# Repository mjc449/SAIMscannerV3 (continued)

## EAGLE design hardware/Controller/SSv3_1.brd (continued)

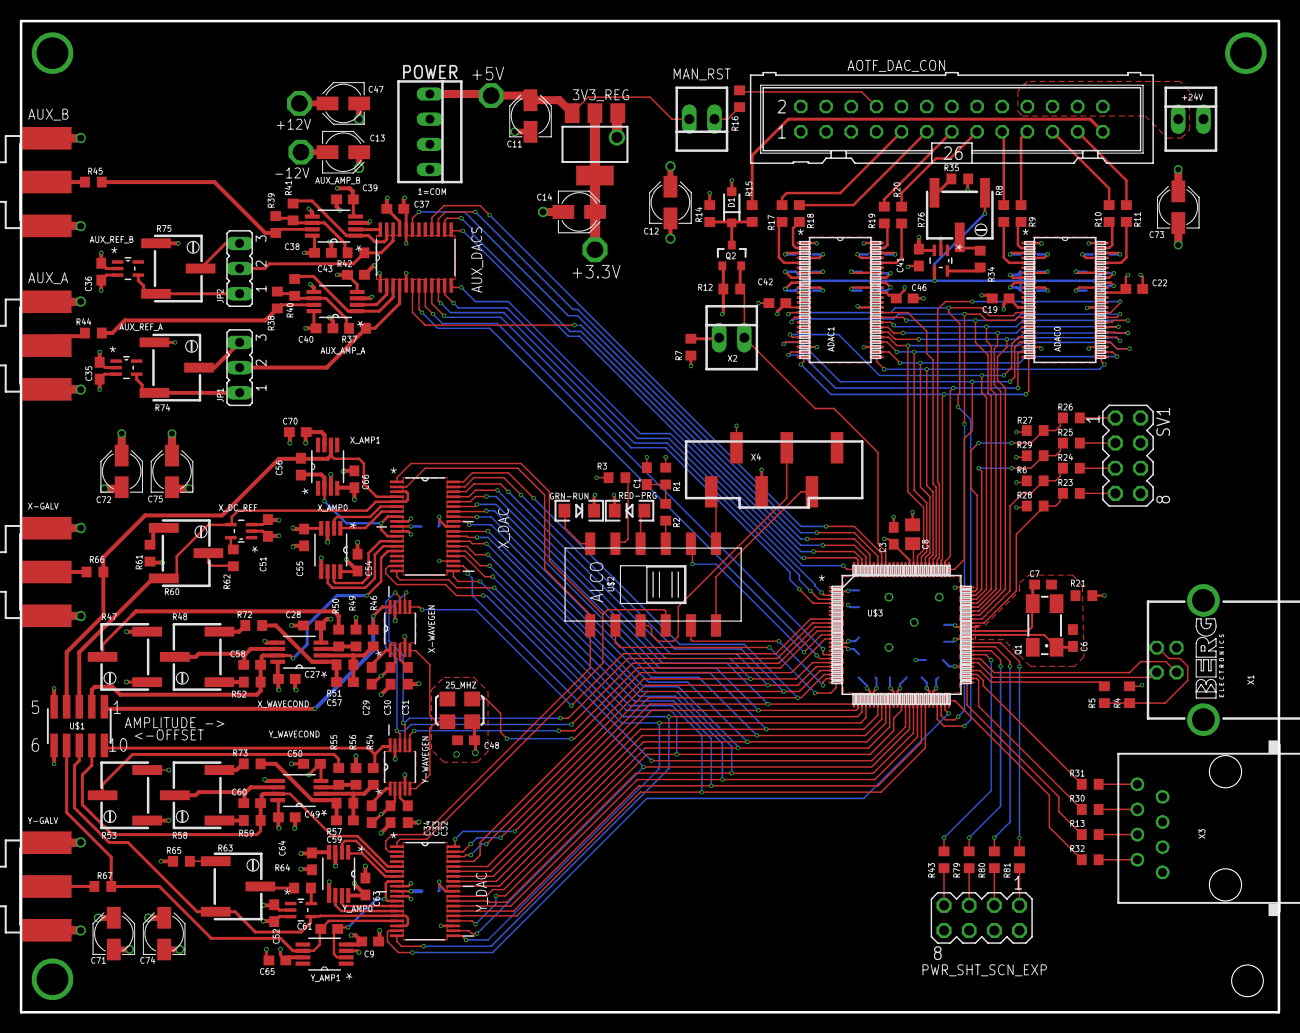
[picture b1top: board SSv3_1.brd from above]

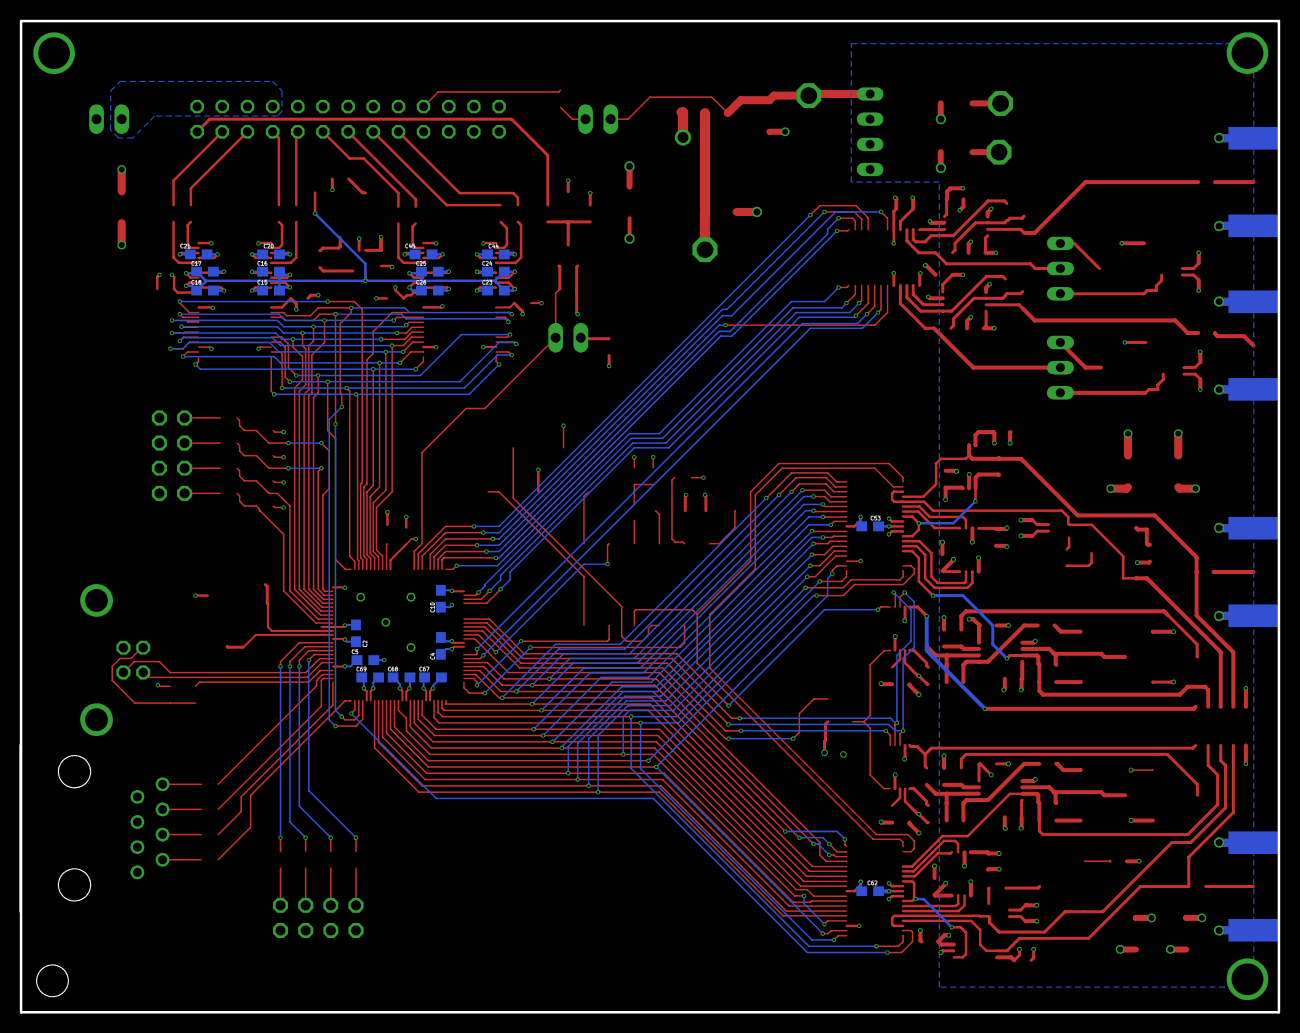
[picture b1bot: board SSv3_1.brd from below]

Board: 4 copper layers, 127.0 x 100.1 mm, 197 parts (21 on the bottom side), 190 nets.

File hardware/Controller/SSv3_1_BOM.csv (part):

"Part";"Value";"Device";"Package";"Description";"MANUFACTURER_PART_NUMBER";"MF";"MPN";"OC_FARNELL";"OC_NEWARK";"PACKAGE";"PROD_ID";"SUPPLIER";"VALUE";"VENDOR";
"+3.3V";"TESTPOINT";"TESTPOINT";"TESTPOINT";"";"";"";"";"";"";"";"";"";"";"";
"+5V";"TESTPOINT";"TESTPOINT";"TESTPOINT";"";"";"";"";"";"";"";"";"";"";"";
"+12V";"TESTPOINT";"TESTPOINT";"TESTPOINT";"";"";"";"";"";"";"";"";"";"";"";
"+24V";"AOTF_SUPPLY";"2PINHEADER";"22-23-2021";"2 pin 0.100" Header for 2 pin header pigtails I get from Allelectronics.";"";"";"";"";"";"";"";"";"";"";
"-12V";"TESTPOINT";"TESTPOINT";"TESTPOINT";"";"";"";"";"";"";"";"";"";"";"";
"3V3_REG";"AP1117";"AP1117E33G_REG";"SOT223";"3.3 volt 1 amp regulator SOT223 case";"";"";"";"";"";"";"";"";"";"";
"25_MHZ";"ASFL1";"ASFL1";"ASF";"CRYSTAL CLOCK OSCILLATORS";"";"Abracon Corporation";"ASFL1-125.000MHZ-EC-T";"1838931";"19M1882";"";"";"";"";"";
"ADAC0";"AD5583YRVZ";"AD5583YRVZ";"RV_48";"";"AD5583YRVZ";"";"";"";"";"";"";"";"";"Vendor";
"ADAC1";"AD5583YRVZ";"AD5583YRVZ";"RV_48";"";"AD5583YRVZ";"";"";"";"";"";"";"";"";"Vendor";
"ADAC_REF";"ADR01";"ADR03AKSZ-REEL7";"SOT65P210X110-5N";"Ultracompact, Precision 10.0 V/5.0 V/2.5 V/3.0 V Voltage References";"";"";"ADR03AKSZ-REEL7";"1838919";"59K2675";"SC70-5";"";"Analog Devices";"";"";
"AOTF_DAC_CON";"TO_PNLMNT_DB25";"ML26";"ML26";"HARTING";"";"";"";"unknown";"unknown";"";"";"";"";"";
"AUX_A";"";"SMA_SMT";"SIDE_MOUNTSMA";"SMA 50 Ohm End Launch Jack Receptacle - Round Contact";"";"";"";"";"";"";"";"";"";"";
"AUX_AMP_A";"OP2177";"OP2177ARMZ-R7";"SOP65P490X110-8N";"Operational Amplifiers";"";"";"OP2177ARMZ-R7";"-";"71P5435";"MSOP-8";"";"Analog Devices";"";"";
"AUX_AMP_B";"OP2177";"OP2177ARMZ-R7";"SOP65P490X110-8N";"Operational Amplifiers";"";"";"OP2177ARMZ-R7";"-";"71P5435";"MSOP-8";"";"Analog Devices";"";"";
"AUX_B";"";"SMA_SMT";"SIDE_MOUNTSMA";"SMA 50 Ohm End Launch Jack Receptacle - Round Contact";"";"";"";"";"";"";"";"";"";"";
"AUX_DACS";"AD5440YRUZ";"AD5440YRUZTSSOP-24";"SOP65P640X120-24N";"";"";"";"";"";"";"";"";"";"";"";
"AUX_REF_A";"ADR01";"ADR03AKSZ-REEL7";"SOT65P210X110-5N";"Ultracompact, Precision 10.0 V/5.0 V/2.5 V/3.0 V Voltage References";"";"";"ADR03AKSZ-REEL7";"1838919";"59K2675";"SC70-5";"";"Analog Devices";"";"";
"AUX_REF_B";"ADR01";"ADR03AKSZ-REEL7";"SOT65P210X110-5N";"Ultracompact, Precision 10.0 V/5.0 V/2.5 V/3.0 V Voltage References";"";"";"ADR03AKSZ-REEL7";"1838919";"59K2675";"SC70-5";"";"Analog Devices";"";"";
"C1";"0.1uF";"C-USC0603";"C0603";"CAPACITOR, American symbol";"";"";"";"";"";"";"";"";"";"";
"C2";"0.1uF";"C-USC0603";"C0603";"CAPACITOR, American symbol";"";"";"";"";"";"";"";"";"";"";
"C3";"0.1uF";"C-USC0603";"C0603";"CAPACITOR, American symbol";"";"";"";"";"";"";"";"";"";"";
"C4";"0.1uF";"C-USC0603";"C0603";"CAPACITOR, American symbol";"";"";"";"";"";"";"";"";"";"";
"C5";"0.1uF";"C-USC0603";"C0603";"CAPACITOR, American symbol";"";"";"";"";"";"";"";"";"";"";
"C6";"30pF";"C-USC0603";"C0603";"CAPACITOR, American symbol";"";"";"";"";"";"";"";"";"";"";
"C7";"30pF";"C-USC0603";"C0603";"CAPACITOR, American symbol";"";"";"";"";"";"";"";"";"";"";
"C8";"10uF";"C-USC0805";"C0805";"CAPACITOR, American symbol";"";"";"";"";"";"";"";"";"";"";
"C9";"0.1uF";"C-USC0603";"C0603";"CAPACITOR, American symbol";"";"";"";"";"";"";"";"";"";"";
"C10";"0.1uF";"C-USC0603";"C0603";"CAPACITOR, American symbol";"";"";"";"";"";"";"";"";"";"";
"C11";"10uF";"CPOL-USB";"PANASONIC_B";"POLARIZED CAPACITOR, American symbol";"";"";"";"";"";"";"";"";"";"";
"C12";"10uF";"CPOL-USB";"PANASONIC_B";"POLARIZED CAPACITOR, American symbol";"";"";"";"";"";"";"";"";"";"";
"C13";"10uF";"CPOL-USB";"PANASONIC_B";"POLARIZED CAPACITOR, American symbol";"";"";"";"";"";"";"";"";"";"";
"C14";"10uF";"CPOL-USB";"PANASONIC_B";"POLARIZED CAPACITOR, American symbol";"";"";"";"";"";"";"";"";"";"";
"C15";"0.1uF";"C-USC0603";"C0603";"CAPACITOR, American symbol";"";"";"";"";"";"";"";"";"";"";
"C16";"0.1uF";"C-USC0603";"C0603";"CAPACITOR, American symbol";"";"";"";"";"";"";"";"";"";"";
"C17";"0.1uF";"C-USC0603";"C0603";"CAPACITOR, American symbol";"";"";"";"";"";"";"";"";"";"";
"C18";"0.1uF";"C-USC0603";"C0603";"CAPACITOR, American symbol";"";"";"";"";"";"";"";"";"";"";
"C19";"0.1uF";"C-USC0603";"C0603";"CAPACITOR, American symbol";"";"";"";"";"";"";"";"";"";"";
"C20";"0.1uF";"C-USC0603";"C0603";"CAPACITOR, American symbol";"";"";"";"";"";"";"";"";"";"";
"C21";"0.1uF";"C-USC0603";"C0603";"CAPACITOR, American symbol";"";"";"";"";"";"";"";"";"";"";
"C22";"0.1uF";"C-USC0603";"C0603";"CAPACITOR, American symbol";"";"";"";"";"";"";"";"";"";"";
"C23";"0.1uF";"C-USC0603";"C0603";"CAPACITOR, American symbol";"";"";"";"";"";"";"";"";"";"";
"C24";"0.1uF";"C-USC0603";"C0603";"CAPACITOR, American symbol";"";"";"";"";"";"";"";"";"";"";
"C25";"0.1uF";"C-USC0603";"C0603";"CAPACITOR, American symbol";"";"";"";"";"";"";"";"";"";"";
"C26";"0.1uF";"C-USC0603";"C0603";"CAPACITOR, American symbol";"";"";"";"";"";"";"";"";"";"";
"C27";"0.1uF";"C-USC0603";"C0603";"CAPACITOR, American symbol";"";"";"";"";"";"";"";"";"";"";
"C28";"0.1uF";"C-USC0603";"C0603";"CAPACITOR, American symbol";"";"";"";"";"";"";"";"";"";"";
"C29";"0.01uF";"C-USC0603";"C0603";"CAPACITOR, American symbol";"";"";"";"";"";"";"";"";"";"";
"C30";"0.1uF";"C-USC0603";"C0603";"CAPACITOR, American symbol";"";"";"";"";"";"";"";"";"";"";
"C31";"0.1uF";"C-USC0603";"C0603";"CAPACITOR, American symbol";"";"";"";"";"";"";"";"";"";"";
"C32";"0.1uF";"C-USC0603";"C0603";"CAPACITOR, American symbol";"";"";"";"";"";"";"";"";"";"";
"C33";"0.1uF";"C-USC0603";"C0603";"CAPACITOR, American symbol";"";"";"";"";"";"";"";"";"";"";
"C34";"0.01uF";"C-USC0603";"C0603";"CAPACITOR, American symbol";"";"";"";"";"";"";"";"";"";"";
"C35";"0.1uF";"C-USC0603";"C0603";"CAPACITOR, American symbol";"";"";"";"";"";"";"";"";"";"";
"C36";"0.1uF";"C-USC0603";"C0603";"CAPACITOR, American symbol";"";"";"";"";"";"";"";"";"";"";
"C37";"0.1uF";"C-USC0603";"C0603";"CAPACITOR, American symbol";"";"";"";"";"";"";"";"";"";"";
"C38";"0.1uF";"C-USC0603";"C0603";"CAPACITOR, American symbol";"";"";"";"";"";"";"";"";"";"";
"C39";"0.1uF";"C-USC0603";"C0603";"CAPACITOR, American symbol";"";"";"";"";"";"";"";"";"";"";
"C40";"0.1uF";"C-USC0603";"C0603";"CAPACITOR, American symbol";"";"";"";"";"";"";"";"";"";"";
"C41";"0.1uF";"C-USC0603";"C0603";"CAPACITOR, American symbol";"";"";"";"";"";"";"";"";"";"";
"C42";"0.1uF";"C-USC0603";"C0603";"CAPACITOR, American symbol";"";"";"";"";"";"";"";"";"";"";
"C43";"0.1uF";"C-USC0603";"C0603";"CAPACITOR, American symbol";"";"";"";"";"";"";"";"";"";"";
"C44";"0.1uF";"C-USC0603";"C0603";"CAPACITOR, American symbol";"";"";"";"";"";"";"";"";"";"";
"C45";"0.1uF";"C-USC0603";"C0603";"CAPACITOR, American symbol";"";"";"";"";"";"";"";"";"";"";
"C46";"0.1uF";"C-USC0603";"C0603";"CAPACITOR, American symbol";"";"";"";"";"";"";"";"";"";"";
"C47";"10uF";"CPOL-USB";"PANASONIC_B";"POLARIZED CAPACITOR, American symbol";"";"";"";"";"";"";"";"";"";"";
"C48";"0.1uF";"C-USC0603";"C0603";"CAPACITOR, American symbol";"";"";"";"";"";"";"";"";"";"";
"C49";"0.1uF";"C-USC0603";"C0603";"CAPACITOR, American symbol";"";"";"";"";"";"";"";"";"";"";
"C50";"0.1uF";"C-USC0603";"C0603";"CAPACITOR, American symbol";"";"";"";"";"";"";"";"";"";"";
"C51";"0.1uF";"C-USC0603";"C0603";"CAPACITOR, American symbol";"";"";"";"";"";"";"";"";"";"";
"C52";"0.1uF";"C-USC0603";"C0603";"CAPACITOR, American symbol";"";"";"";"";"";"";"";"";"";"";
"C53";"0.1uF";"C-USC0603";"C0603";"CAPACITOR, American symbol";"";"";"";"";"";"";"";"";"";"";
"C54";"0.1uF";"C-USC0603";"C0603";"CAPACITOR, American symbol";"";"";"";"";"";"";"";"";"";"";
"C55";"0.1uF";"C-USC0603";"C0603";"CAPACITOR, American symbol";"";"";"";"";"";"";"";"";"";"";
"C56";"OPT";"C-USC0603";"C0603";"CAPACITOR, American symbol";"";"";"";"";"";"";"";"";"";"";
"C57";"OPT";"C-USC0603";"C0603";"CAPACITOR, American symbol";"";"";"";"";"";"";"";"";"";"";
"C58";"OPT";"C-USC0603";"C0603";"CAPACITOR, American symbol";"";"";"";"";"";"";"";"";"";"";
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
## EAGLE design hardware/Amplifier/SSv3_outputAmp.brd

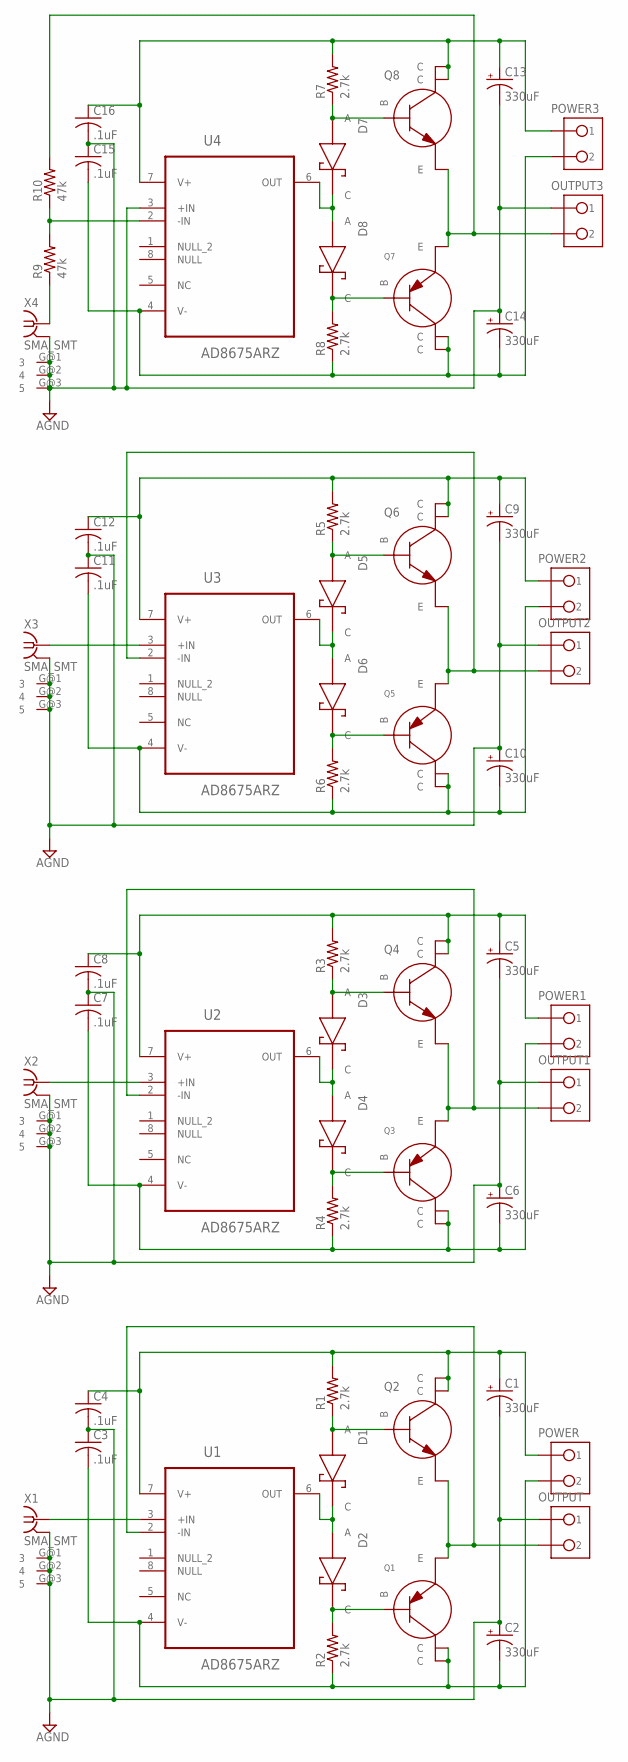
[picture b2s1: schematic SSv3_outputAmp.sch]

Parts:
C1, C2, C5, C6, C9, C10, C13, C14: 330uF; E3,5-8
C3, C4, C7, C8, C11, C12, C15, C16: .1uF; C0603
D1, D2, D3, D4, D5, D6, D7, D8: 1N5819SOD123; SOD-123
OUTPUT, OUTPUT1, OUTPUT2, OUTPUT3: OST-2P-SCREW-TERMINAL
POWER, POWER1, POWER2, POWER3: OST-2P-SCREW-TERMINAL
Q1, Q3, Q5, Q7: NJT4030PSOT-223; SOT223
Q2, Q4, Q6, Q8: NJT4031NSOT-223; SOT223
R1, R2, R3, R4, R5, R6, R7, R8: 2.7k; R0603
R9, R10: 47k; R0603
U1, U2, U3, U4: AD8675ARZ; SOIC127P600X175-8N
X1, X2, X3, X4: SMA_SMT; SIDE_MOUNTSMA

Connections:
+12V: C1.+, C4.1, C5.+, C8.1, C9.+, C12.1, C13.+, C16.1, POWER.P$1 (1), POWER1.P$1 (1), POWER2.P$1 (1), POWER3.P$1 (1), Q2.2 (C), Q2.4 (C), Q4.2 (C), Q4.4 (C), Q6.2 (C), Q6.4 (C), Q8.2 (C), Q8.4 (C), R1.2, R3.2, R5.2, R7.2, U1.7 (V+), U2.7 (V+), U3.7 (V+), U4.7 (V+)
-12V: C2.-, C3.2, C6.-, C7.2, C10.-, C11.2, C14.-, C15.2, POWER.P$2 (2), POWER1.P$2 (2), POWER2.P$2 (2), POWER3.P$2 (2), Q1.2 (C), Q1.4 (C), Q3.2 (C), Q3.4 (C), Q5.2 (C), Q5.4 (C), Q7.2 (C), Q7.4 (C), R2.1, R4.1, R6.1, R8.1, U1.4 (V-), U2.4 (V-), U3.4 (V-), U4.4 (V-)
AGND: C1.-, C2.+, C3.1, C4.2, C5.-, C6.+, C7.1, C8.2, C9.-, C10.+, C11.1, C12.2, C13.-, C14.+, C15.1, C16.2, OUTPUT.P$1 (1), OUTPUT1.P$1 (1), OUTPUT2.P$1 (1), OUTPUT3.P$1 (1), U4.3 (+IN), X1.G@1 (3), X1.G@2 (4), X1.G@3 (5), X1.G@4 (2), X2.G@1 (3), X2.G@2 (4), X2.G@3 (5), X2.G@4 (2), X3.G@1 (3), X3.G@2 (4), X3.G@3 (5), X3.G@4 (2), X4.G@1 (3), X4.G@2 (4), X4.G@3 (5), X4.G@4 (2)
unnamed: D1.C, D2.A, U1.6 (OUT)
unnamed: D1.A, Q2.1 (B), R1.1
unnamed: D2.C, Q1.1 (B), R2.2
unnamed: D3.C, D4.A, U2.6 (OUT)
unnamed: D3.A, Q4.1 (B), R3.1
unnamed: D4.C, Q3.1 (B), R4.2
unnamed: U1.3 (+IN), X1.1
unnamed: U2.3 (+IN), X2.1
unnamed: D5.C, D6.A, U3.6 (OUT)
unnamed: D5.A, Q6.1 (B), R5.1
unnamed: D6.C, Q5.1 (B), R6.2
unnamed: U3.3 (+IN), X3.1
unnamed: D7.C, D8.A, U4.6 (OUT)
unnamed: D7.A, Q8.1 (B), R7.1
unnamed: D8.C, Q7.1 (B), R8.2
unnamed: R9.1, X4.1
unnamed: R9.2, R10.1, U4.2 (-IN)
VOUT: OUTPUT.P$2 (2), Q1.3 (E), Q2.3 (E), U1.2 (-IN)
VOUT1: OUTPUT1.P$2 (2), Q3.3 (E), Q4.3 (E), U2.2 (-IN)
VOUT2: OUTPUT2.P$2 (2), Q5.3 (E), Q6.3 (E), U3.2 (-IN)
VOUT3: OUTPUT3.P$2 (2), Q7.3 (E), Q8.3 (E), R10.2

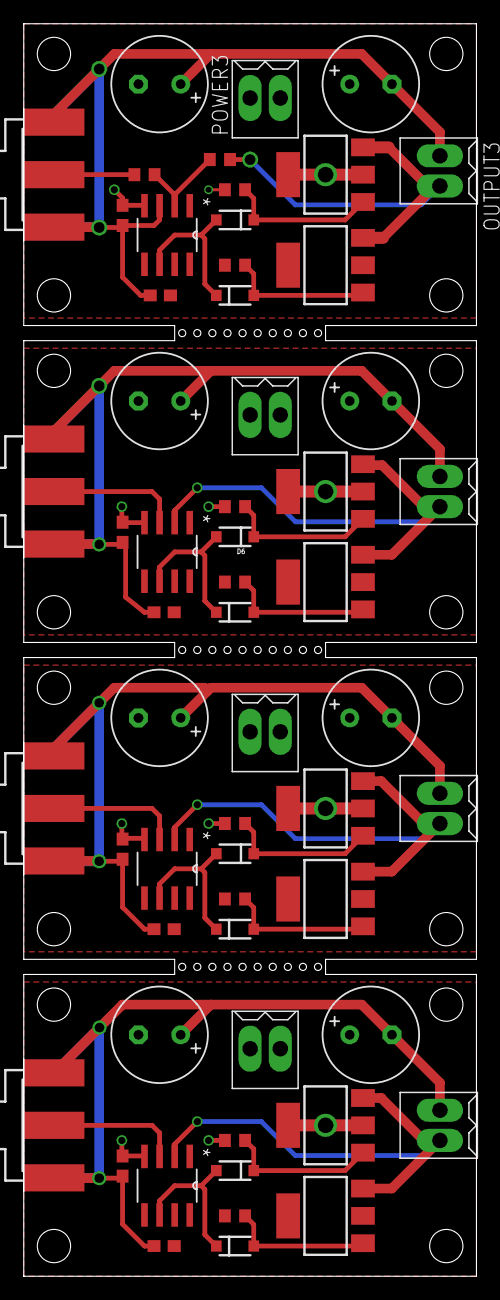
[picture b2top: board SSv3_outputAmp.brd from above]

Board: 2 copper layers, 38.1 x 105.4 mm, 58 parts (0 on the bottom side), 24 nets.

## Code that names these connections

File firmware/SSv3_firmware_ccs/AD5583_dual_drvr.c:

/*
Library for using two AD5583 quad channel 10 bit DACs for DC output 
to the AOTF controller on the SAIMScannerV3 hardware.
The chips are configured for simultaneous synchronous loads, data must be
latched serially

Basic IO macros are defined in firmwave_0_0.h:
   X_AMP sets the X amplitude address bits
   X_DC sets the X DC bias address bits
   Y_AMP sets the Y amplitude address bits
   Y_DC sets the Y DC bias address bits
   
   X_WRITE pulses the X write pin
   Y_WRITE pulses the Y write pin
   GDAC_LOAD pulses the load pin on both DACs, updating all 4 outputs

Copyright 2019 Marshall J. Colville (mjc449@cornell.edu)

Redistribution and use in source and binary forms, with or without modification,
are permitted provided that the following conditions are met:

1. Redistributions of source code must retain the above copyright notice,
this list of conditions and the following disclaimer.

2. Redistributions in binary form must reproduce the above copyright notice,
this list of conditions and the following disclaimer in the documentation and/or
other materials provided with the distribution.

THIS SOFTWARE IS PROVIDED BY THE COPYRIGHT HOLDERS AND CONTRIBUTORS "AS IS" AND
ANY EXPRESS OR IMPLIED WARRANTIES, INCLUDING, BUT NOT LIMITED TO, THE IMPLIED
WARRANTIES OF MERCHANTABILITY AND FITNESS FOR A PARTICULAR PURPOSE ARE DISCLAIMED.
IN NO EVENT SHALL THE COPYRIGHT HOLDER OR CONTRIBUTORS BE LIABLE FOR ANY DIRECT,
INDIRECT, INCIDENTAL, SPECIAL, EXEMPLARY, OR CONSEQUENTIAL DAMAGES (INCLUDING,
BUT NOT LIMITED TO, PROCUREMENT OF SUBSTITUTE GOODS OR SERVICES; LOSS OF USE,
DATA, OR PROFITS; OR BUSINESS INTERRUPTION) HOWEVER CAUSED AND ON ANY THEORY OF
LIABILITY, WHETHER IN CONTRACT, STRICT LIABILITY, OR TORT (INCLUDING NEGLIGENCE
OR OTHERWISE) ARISING IN ANY WAY OUT OF THE USE OF THIS SOFTWARE, EVEN IF ADVISED
OF THE POSSIBILITY OF SUCH DAMAGE.
*/

#define ADAC_LOAD bit_clear(LATD, 14); bit_set(LATD, 14);
#define ADAC0_WR bit_clear(LATD, 12); bit_set(LATD, 12);
#define ADAC1_WR bit_clear(LATD, 13); bit_set(LATD, 13);
#define ADAC_RS bit_clear(LATD, 15); bit_set(LATD, 15);
#define CHA bit_clear(LATD, 11); bit_clear(LATD, 10);
#define CHB bit_clear(LATD, 11); bit_set(LATD, 10);
#define CHC bit_set(LATD, 11); bit_clear(LATD, 10);
#define CHD bit_set(LATD, 11); bit_set(LATD, 11);

//Global variables
const size_t MaxAOTF = 32;
static int* AOTFArray[MaxAOTF][8];  //Addresses of the AOTF profile locations on the heap

//Update the data registers on a ADAC channel, must be followed an external call to ADAC_LOAD
void update_ADAC_channel(int8* pChannel, int* pValue)
{

   if(*pValue > 0x03FF)  //Check that the value is within range
      *pValue = 0x03FF;  //If it's too big, set it to max
   
   switch(*pChannel)
   {
      case 7:
         output_d(0b1111000000000000 | *pValue);
         ADAC1_WR;
         break;
      case 6:
         output_d(0b1111010000000000 | *pValue);
         ADAC1_WR;
         break;
      case 5:
         output_d(0b1111100000000000 | *pValue);
         ADAC1_WR;
         break;
      case 4:
         output_d(0b1111110000000000 | *pValue);
         ADAC1_WR;
         break;
      case 3:
         output_d(0b1111000000000000 | *pValue);
         ADAC0_WR;
         break;
      case 2:
         output_d(0b1111010000000000 | *pValue);
         ADAC0_WR;
         break;
      case 1:
         output_d(0b1111100000000000 | *pValue);
         ADAC0_WR;
         break;
      case 0:
         output_d(0b1111110000000000 | *pValue);
         ADAC0_WR;
         break;
      default:
         output_error(5);
         break;
   }
}

//Update all 8 AOTF channels, must be followed by an external call to ADAC_LOAD
void update_ADAC_all(int* pProfile)
{
   if(pProfile)  //Check that the profile exists
   {
      int8 channel = 0;
      for(int i = 0; i <= 7; i++)
      {
         update_ADAC_channel(&channel, pProfile++);
         channel++;
      }
   }
   else  //If the profile is NULL (deleted or unassigned)
      output_error(5);  //AOTF errors are 5 blinks
}

//Creates a new ADAC profile on the heap and returns a pointer to the profile
//Returns 0 if the operation succeeds, 1 if it fails
int new_ADAC_profile(int8* pCommand)
{
   int num = *pCommand++;
   for (int i = 0; i <= 7; i++)  //Add the value for each channel
      AOTFArray[num][i] = make16(*(pCommand++),*(pCommand++));
   return(0);
}

int load_AOTF_profile(int Profile)
{
   if(Profile >= MaxAOTF)
   {
      output_error(5);
      return 2;
   }
   update_ADAC_all(&AOTFArray[Profile][0]);  //Load the requested profile
   ADAC_LOAD;  //Update the DAC output
   return 0;
}

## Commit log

2018-05-20 Set theme jekyll-theme-minimal
2019-01-28 Initial commit of the full project repository
2019-01-29 Finished adding license to files. Added .pdf of the hardware. Added .zip with current software build.
2019-01-29 Deleted current build from repository
2019-01-29 Deleted old LICENSE and HIDAPI testgui.exe
2019-01-29 Added analysis projects
2019-01-29 Re-adding analysis
2019-01-29 Re-added analysis project
2019-01-30 Update issue templates
2019-02-01 Updated license in software to BSD
2019-02-01 Fixed end of license
2019-02-03 Updated license info in about
2019-02-04 Added enclosure panel files from Front Panel Designer. These have not been tested, but are translated from the current design.
2019-02-04 update to license
2019-02-08 First Commit Software Manuel
2019-02-10 Initial commit on new branch with BOM. Need to fill in digikey PNs and prices.
2019-02-12 Small changes
2019-02-12 Added docgen.sh to generate documentation for the project using doxygen. Currently only works for the driver API.
2019-02-12 Added BOM for controller components
2019-02-12 Updated local settings for UI solution
2019-02-13 Working on BOM and tidying up wire stubs on board
2019-02-13 First commit of firmware port from CCS to MPlabX
2019-02-15 Almost finished with updated BOM
2019-02-19 First commit with modified microchip bootloader and beginning of new firmware framework for micro-manager integration
2019-02-20 Added microchip firmware and bootloader
2019-02-20 Finished merging hardware_dev branch
2019-02-20 Cleaned up DRC warnings from switch to Eagle 9.3
2019-02-20 Updated mc_firmware project
2019-02-22 Finished BOM from Digikey for components and connectors.
2019-02-26 First commit in development branch for micro-manager integration
2019-02-27 Initial commit on branch for building an analysis GUI
2019-02-27 Added labels to enclosure panels
2019-03-01 Added images for enclosure panels.
2019-03-05 Added new sticker layout for clear vinyl front and back panel layout
2019-03-06 Began bootloader manual.
2019-03-06 Added .gitattributes to use pandoc for diffing .docx
2019-03-08 Working on bootloader doc
2019-03-08 Deleted temp Word file
2019-03-08 working
2019-03-15 Updated bootloader to check if there is valid application code. If the application is empty the device remains in bootloader. Also, the bootloader flag is not cleared until SW reset from bootloader a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
2019-03-15 committing prior to merge MM_dev branch
2019-03-15 Repeat previous commit
2019-03-15 Removed private/local files from MPLabX projects
2019-03-16 Working on bootloader manual. Also found a couple errors in bootloader flag code manipulation.
2019-07-17 Added a command set table with brief descriptions
2019-07-18 Finished first draft of command set for firmware
